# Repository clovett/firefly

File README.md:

# firefly

See [wiki](https://github.com/clovett/firefly/wiki)

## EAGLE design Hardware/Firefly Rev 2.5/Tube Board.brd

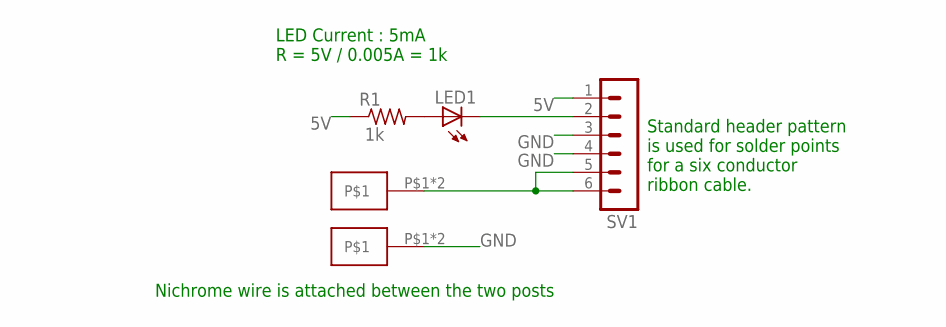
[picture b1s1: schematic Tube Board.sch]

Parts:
LED1: LED_ESML0603; LED_SML0603
R1: R-US_R0603; R0603
SV1: MA06-1
U$1, U$2: A29938CT

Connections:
5V: R1.1, SV1.1
GND: SV1.3, SV1.4, U$2.P$1, U$2.P$2
unnamed: SV1.5, SV1.6, U$1.P$1, U$1.P$2
unnamed: LED1.A, R1.2
unnamed: LED1.C, SV1.2

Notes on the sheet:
Nichrome wire is attached between the two posts
LED Current : 5mA R = 5V / 0.005A = 1k
Standard header pattern is used for solder points for a six conductor ribbon cable.

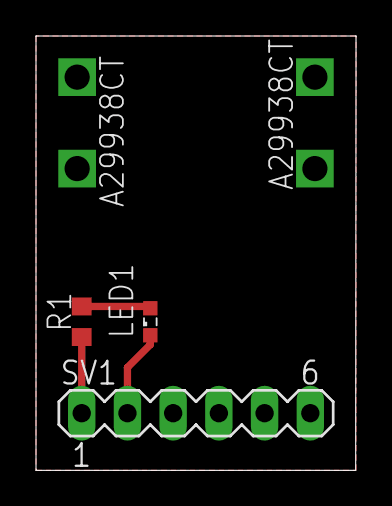
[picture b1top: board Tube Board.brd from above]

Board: 2 copper layers, 17.8 x 24.1 mm, 5 parts (0 on the bottom side), 5 nets.

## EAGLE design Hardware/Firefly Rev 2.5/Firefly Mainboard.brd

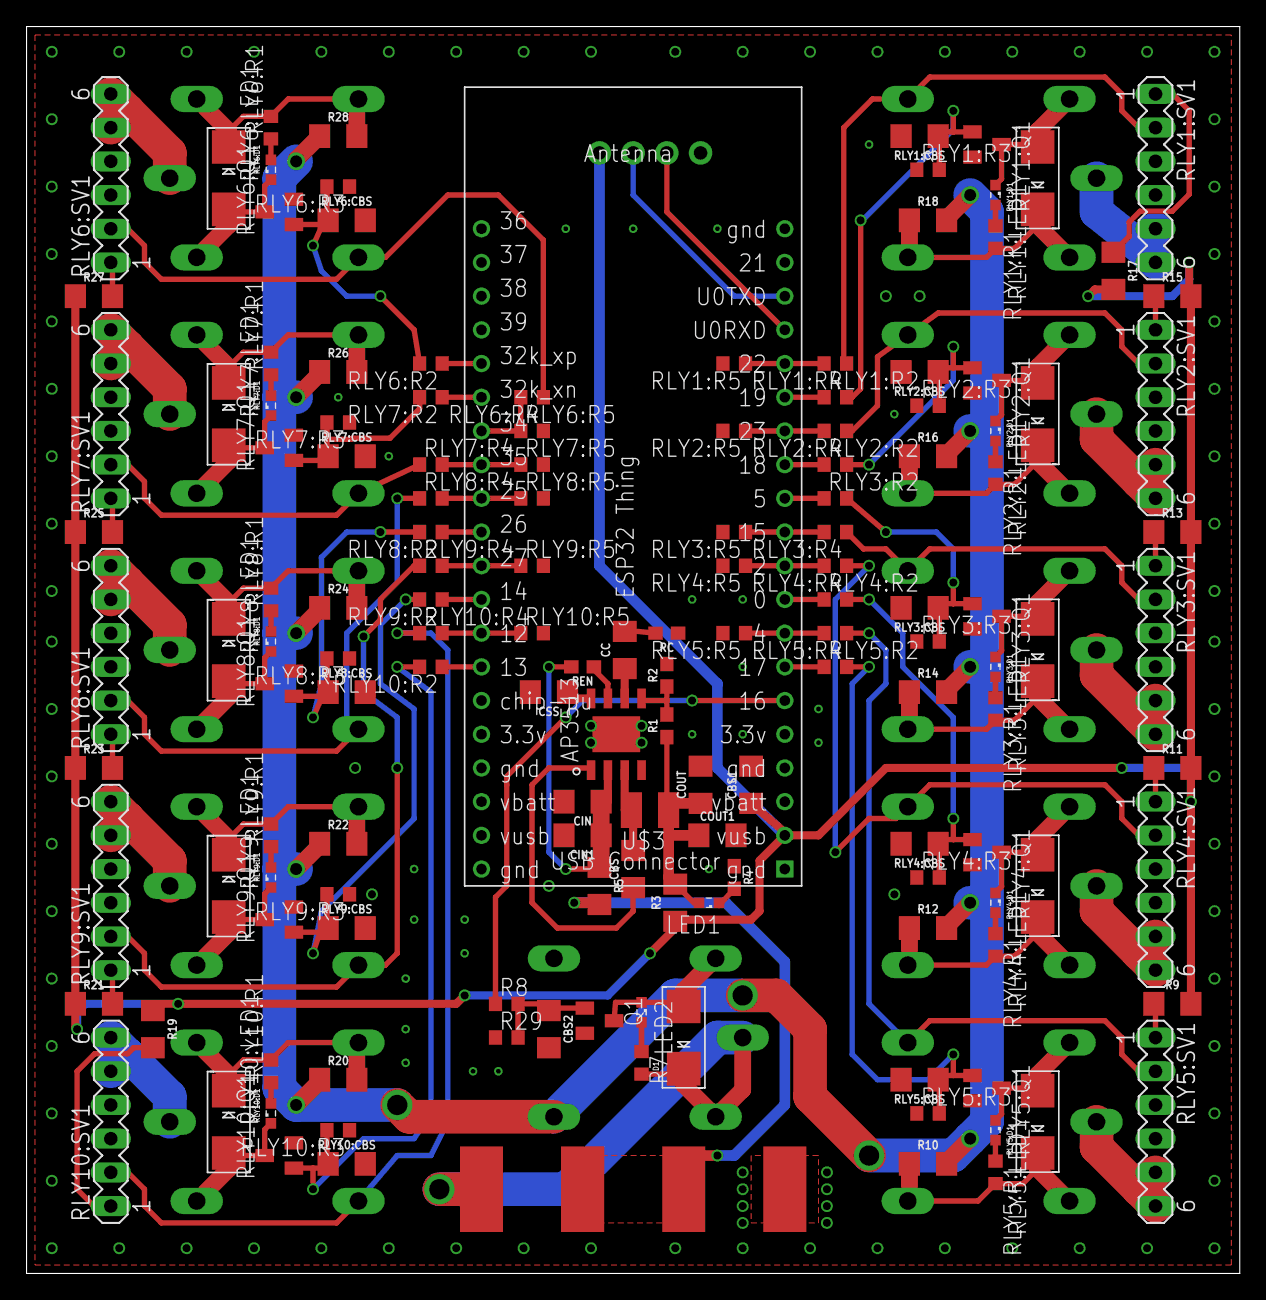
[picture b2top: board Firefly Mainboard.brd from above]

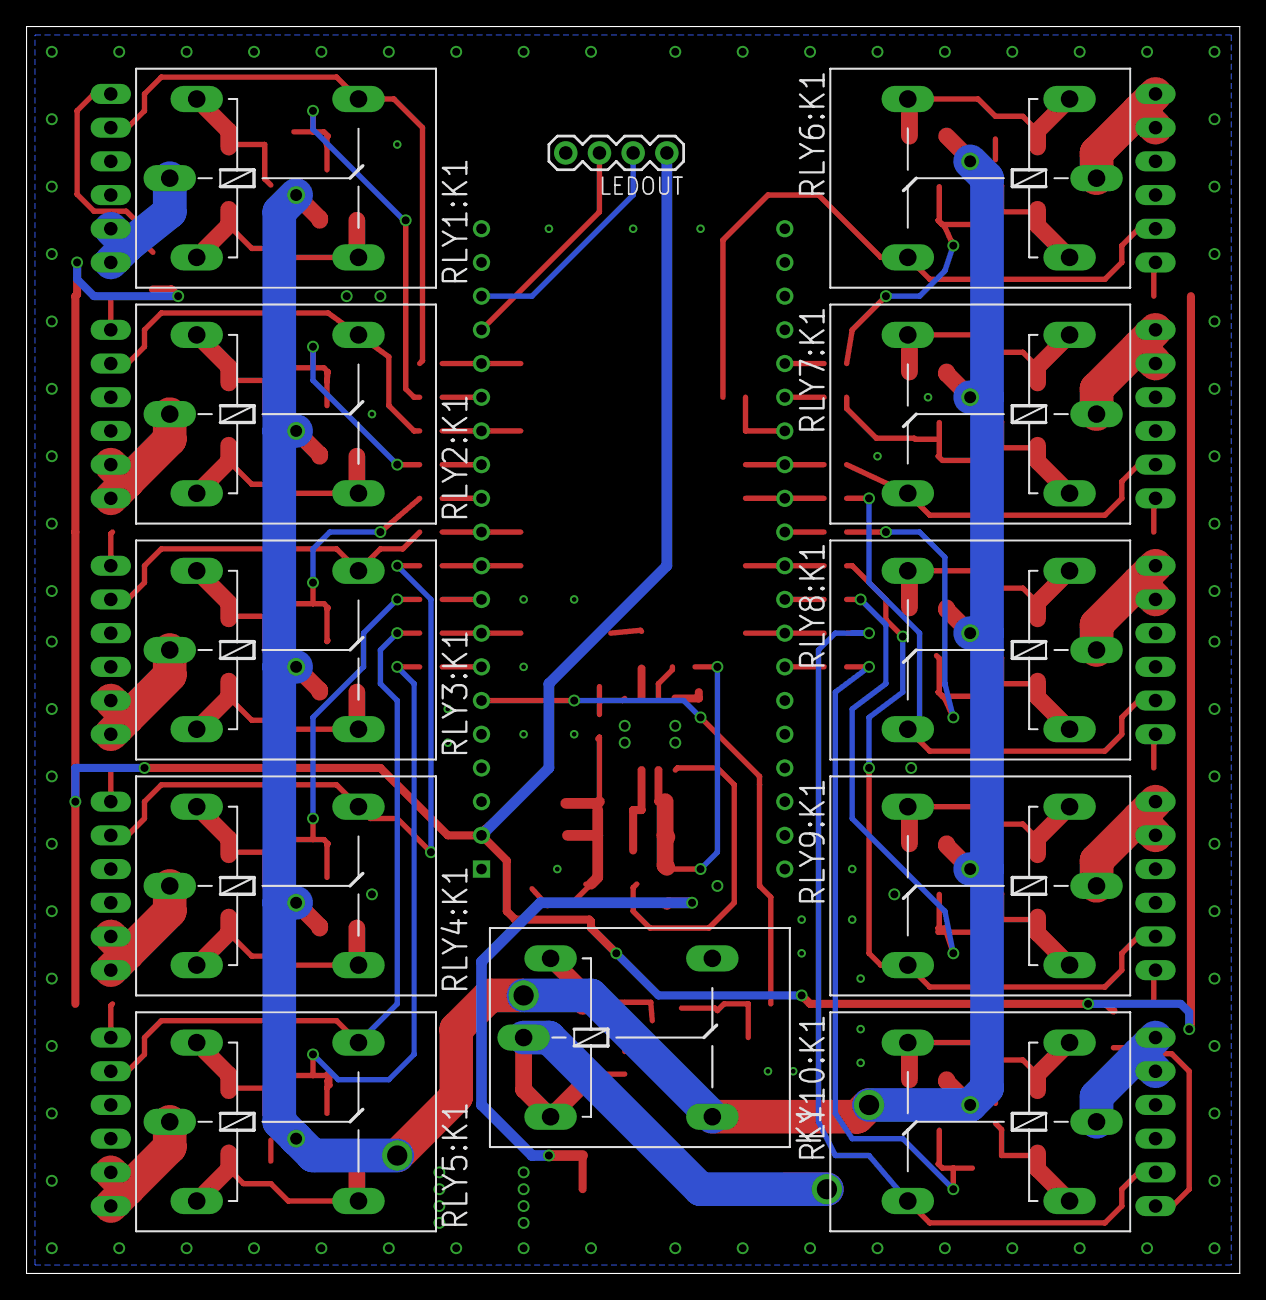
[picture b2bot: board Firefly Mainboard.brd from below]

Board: 2 copper layers, 91.4 x 94.0 mm, 160 parts (12 on the bottom side), 111 nets.

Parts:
CBS: 10nF; 1206
CBS1: 0.1uF; 1206
CBS2: 220nF; 1206
CC: 3.3nF; 1206
CIN, CIN1: 10uF; 1206
COUT, COUT1: 22uF; 1206
CSS: 1.0uF; 1206
D1: SMADIODE
K1: G5LE
LED1, LED2: LED_SML0603
LEDOUT: 1X4-BIG; 1X04-BIG
Q1: BCF32SMD; SOT23-BEC
R1: 10k\; 0603
R2: 2.26k; 0603
R3, R5, R9, R10, R11, R12, R13, R14, R15, R16, R17, R18, R19, R20, R21, R22, R23, R24, R25, R26, R27, R28: 0; 1206
R4: 1k; 0603
R7, R8: R0603
R29: 10k; R0603
RC: 13k; 0603
REN: 100k; 0603
RLY1:CBS, RLY2:CBS, RLY3:CBS, RLY4:CBS, RLY5:CBS, RLY6:CBS, RLY7:CBS, RLY8:CBS, RLY9:CBS, RLY10:CBS: 220nF; 1206
RLY1:D1, RLY2:D1, RLY3:D1, RLY4:D1, RLY5:D1, RLY6:D1, RLY7:D1, RLY8:D1, RLY9:D1, RLY10:D1: SMADIODE
RLY1:K1, RLY2:K1, RLY3:K1, RLY4:K1, RLY5:K1, RLY6:K1, RLY7:K1, RLY8:K1, RLY9:K1, RLY10:K1: G5LE
RLY1:LED1, RLY2:LED1, RLY3:LED1, RLY4:LED1, RLY5:LED1, RLY6:LED1, RLY7:LED1, RLY8:LED1, RLY9:LED1, RLY10:LED1: LED_SML0603
RLY1:Q1, RLY2:Q1, RLY3:Q1, RLY4:Q1, RLY5:Q1, RLY6:Q1, RLY7:Q1, RLY8:Q1, RLY9:Q1, RLY10:Q1: BCF32SMD; SOT23-BEC
RLY1:R1, RLY1:R2, RLY2:R1, RLY2:R2, RLY3:R1, RLY3:R2, RLY4:R1, RLY4:R2, RLY5:R1, RLY5:R2, RLY6:R1, RLY6:R2, RLY7:R1, RLY7:R2, RLY8:R1, RLY8:R2, RLY9:R1, RLY9:R2, RLY10:R1, RLY10:R2: R0603
RLY1:R3, RLY1:R4, RLY2:R3, RLY2:R4, RLY3:R3, RLY3:R4, RLY4:R3, RLY4:R4, RLY5:R3, RLY5:R4, RLY6:R3, RLY6:R4, RLY7:R3, RLY7:R4, RLY8:R3, RLY8:R4, RLY9:R3, RLY9:R4, RLY10:R3, RLY10:R4: 10k; R0603
RLY1:R5, RLY2:R5, RLY3:R5, RLY4:R5, RLY5:R5, RLY6:R5, RLY7:R5, RLY8:R5, RLY9:R5, RLY10:R5: 15k; R0603
RLY1:SV1, RLY2:SV1, RLY3:SV1, RLY4:SV1, RLY5:SV1, RLY6:SV1, RLY7:SV1, RLY8:SV1, RLY9:SV1, RLY10:SV1: MA06-1
U$1: ESP32_THING
U$2: AP3513E
U$3: L 4.7uH; R1210
U$4, U$5: BATTERY_PADS

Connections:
+5V: CBS1.1, LEDOUT.1, R3.1, R9.2, R11.2, R13.2, R15.2, R17.2, R19.1, R21.1, R23.1, R25.1, R27.1, U$1.P$2
+12V: K1.S, R10.2, R12.2, R14.2, R16.2, R18.2, R20.1, R22.1, R24.1, R26.1, R28.1
EN_RELAY: R8.1, U$1.P$6
GND: CBS1.2, CBS2.2, CIN.2, CIN1.2, COUT.2, COUT1.2, CSS.2, LEDOUT.4, Q1.E, R2.2, R4.1, R29.1, RC.1, RLY1:CBS.2, RLY1:Q1.E, RLY1:R3.1, RLY1:R5.2, RLY1:SV1.3, RLY1:SV1.4, RLY2:CBS.2, RLY2:Q1.E, RLY2:R3.1, RLY2:R5.2, RLY2:SV1.3, RLY2:SV1.4, RLY3:CBS.2, RLY3:Q1.E, RLY3:R3.1, RLY3:R5.2, RLY3:SV1.3, RLY3:SV1.4, RLY4:CBS.2, RLY4:Q1.E, RLY4:R3.1, RLY4:R5.2, RLY4:SV1.3, RLY4:SV1.4, RLY5:CBS.2, RLY5:Q1.E, RLY5:R3.1, RLY5:R5.2, RLY5:SV1.3, RLY5:SV1.4, RLY6:CBS.2, RLY6:Q1.E, RLY6:R3.1, RLY6:R5.2, RLY6:SV1.3, RLY6:SV1.4, RLY7:CBS.2, RLY7:Q1.E, RLY7:R3.1, RLY7:R5.2, RLY7:SV1.3, RLY7:SV1.4, RLY8:CBS.2, RLY8:Q1.E, RLY8:R3.1, RLY8:R5.2, RLY8:SV1.3, RLY8:SV1.4, RLY9:CBS.2, RLY9:Q1.E, RLY9:R3.1, RLY9:R5.2, RLY9:SV1.3, RLY9:SV1.4, RLY10:CBS.2, RLY10:Q1.E, RLY10:R3.1, RLY10:R5.2, RLY10:SV1.3, RLY10:SV1.4, U$1.P$1, U$1.P$20, U$1.P$21, U$1.P$24, U$2.EP, U$2.GND, U$4.P2
unnamed: R1.2, R2.1, U$2.FB
unnamed: CC.1, U$2.COMP
unnamed: CC.2, RC.2
unnamed: CSS.1, U$2.SS
unnamed: REN.1, U$2.EN
unnamed: LEDOUT.2, U$1.P$18
unnamed: CBS.2, U$2.SW, U$3.2
unnamed: CBS.1, U$2.BS
unnamed: RLY5:R2.1, U$1.P$7
unnamed: RLY5:R4.2, RLY5:R5.1, U$1.P$8
unnamed: RLY4:R2.1, U$1.P$9
unnamed: RLY4:R4.2, RLY4:R5.1, U$1.P$10
unnamed: RLY3:R2.1, U$1.P$12
unnamed: RLY3:R4.2, RLY3:R5.1, U$1.P$11
unnamed: RLY2:R2.1, U$1.P$13
unnamed: RLY2:R4.2, RLY2:R5.1, U$1.P$14
unnamed: RLY10:R2.1, U$1.P$27
unnamed: RLY10:R4.2, RLY10:R5.1, U$1.P$28
unnamed: RLY9:R2.1, U$1.P$29
unnamed: RLY9:R4.2, RLY9:R5.1, U$1.P$30
unnamed: RLY8:R2.1, U$1.P$31
unnamed: RLY8:R4.2, RLY8:R5.1, U$1.P$32
unnamed: RLY7:R2.1, U$1.P$35
unnamed: RLY7:R4.2, RLY7:R5.1, U$1.P$33
unnamed: RLY6:R2.1, U$1.P$36
unnamed: RLY6:R4.2, RLY6:R5.1, U$1.P$34
unnamed: COUT.1, COUT1.1, LED1.A, R1.1, R3.2, U$3.1
unnamed: LED1.C, R4.2
unnamed: D1.A, K1.2, LED2.C, Q1.C
unnamed: RLY1:R2.1, U$1.P$15
unnamed: CIN.1, CIN1.1, R5.1, REN.2, U$2.IN
unnamed: LED2.A, R7.1
unnamed: R10.1, RLY5:D1.C, RLY5:K1.1, RLY5:K1.S, RLY5:R1.2
unnamed: R9.1, RLY5:SV1.1
unnamed: R11.1, RLY4:SV1.1
unnamed: R12.1, RLY4:D1.C, RLY4:K1.1, RLY4:K1.S, RLY4:R1.2
unnamed: R13.1, RLY3:SV1.1
unnamed: R14.1, RLY3:D1.C, RLY3:K1.1, RLY3:K1.S, RLY3:R1.2
unnamed: R15.1, RLY2:SV1.1
unnamed: R16.1, RLY2:D1.C, RLY2:K1.1, RLY2:K1.S, RLY2:R1.2
unnamed: R17.1, RLY1:SV1.1
unnamed: R18.1, RLY1:D1.C, RLY1:K1.1, RLY1:K1.S, RLY1:R1.2
unnamed: R19.2, RLY10:SV1.1
unnamed: R20.2, RLY10:D1.C, RLY10:K1.1, RLY10:K1.S, RLY10:R1.2
unnamed: R21.2, RLY9:SV1.1
unnamed: R22.2, RLY9:D1.C, RLY9:K1.1, RLY9:K1.S, RLY9:R1.2
unnamed: R23.2, RLY8:SV1.1
unnamed: R24.2, RLY8:D1.C, RLY8:K1.1, RLY8:K1.S, RLY8:R1.2
unnamed: R25.2, RLY7:SV1.1
unnamed: R26.2, RLY7:D1.C, RLY7:K1.1, RLY7:K1.S, RLY7:R1.2
unnamed: R27.2, RLY6:SV1.1
unnamed: R28.2, RLY6:D1.C, RLY6:K1.1, RLY6:K1.S, RLY6:R1.2
unnamed: RLY1:R4.2, RLY1:R5.1, U$1.P$16
unnamed: D1.C, K1.1, K1.P, R7.2, U$5.P1
unnamed: CBS2.1, Q1.B, R8.2, R29.2
RLY1:N$1: RLY1:LED1.A, RLY1:R1.1
RLY1:N$2: RLY1:K1.P, RLY1:SV1.5, RLY1:SV1.6
RLY1:N$3: RLY1:CBS.1, RLY1:Q1.B, RLY1:R2.2, RLY1:R3.2
RLY1:N$4: RLY1:D1.A, RLY1:K1.2, RLY1:LED1.C, RLY1:Q1.C
RLY1:N$6: RLY1:K1.O, RLY1:R4.1, RLY1:SV1.2
RLY2:N$1: RLY2:LED1.A, RLY2:R1.1
RLY2:N$2: RLY2:K1.P, RLY2:SV1.5, RLY2:SV1.6
RLY2:N$3: RLY2:CBS.1, RLY2:Q1.B, RLY2:R2.2, RLY2:R3.2
RLY2:N$4: RLY2:D1.A, RLY2:K1.2, RLY2:LED1.C, RLY2:Q1.C
RLY2:N$6: RLY2:K1.O, RLY2:R4.1, RLY2:SV1.2
RLY3:N$1: RLY3:LED1.A, RLY3:R1.1
RLY3:N$2: RLY3:K1.P, RLY3:SV1.5, RLY3:SV1.6
RLY3:N$3: RLY3:CBS.1, RLY3:Q1.B, RLY3:R2.2, RLY3:R3.2
RLY3:N$4: RLY3:D1.A, RLY3:K1.2, RLY3:LED1.C, RLY3:Q1.C
RLY3:N$6: RLY3:K1.O, RLY3:R4.1, RLY3:SV1.2
RLY4:N$1: RLY4:LED1.A, RLY4:R1.1
RLY4:N$2: RLY4:K1.P, RLY4:SV1.5, RLY4:SV1.6
RLY4:N$3: RLY4:CBS.1, RLY4:Q1.B, RLY4:R2.2, RLY4:R3.2
RLY4:N$4: RLY4:D1.A, RLY4:K1.2, RLY4:LED1.C, RLY4:Q1.C
RLY4:N$6: RLY4:K1.O, RLY4:R4.1, RLY4:SV1.2
RLY5:N$1: RLY5:LED1.A, RLY5:R1.1
RLY5:N$2: RLY5:K1.P, RLY5:SV1.5, RLY5:SV1.6
RLY5:N$3: RLY5:CBS.1, RLY5:Q1.B, RLY5:R2.2, RLY5:R3.2
RLY5:N$4: RLY5:D1.A, RLY5:K1.2, RLY5:LED1.C, RLY5:Q1.C
RLY5:N$6: RLY5:K1.O, RLY5:R4.1, RLY5:SV1.2
RLY6:N$1: RLY6:LED1.A, RLY6:R1.1
RLY6:N$2: RLY6:K1.P, RLY6:SV1.5, RLY6:SV1.6
RLY6:N$3: RLY6:CBS.1, RLY6:Q1.B, RLY6:R2.2, RLY6:R3.2
RLY6:N$4: RLY6:D1.A, RLY6:K1.2, RLY6:LED1.C, RLY6:Q1.C
RLY6:N$6: RLY6:K1.O, RLY6:R4.1, RLY6:SV1.2
RLY7:N$1: RLY7:LED1.A, RLY7:R1.1
RLY7:N$2: RLY7:K1.P, RLY7:SV1.5, RLY7:SV1.6
RLY7:N$3: RLY7:CBS.1, RLY7:Q1.B, RLY7:R2.2, RLY7:R3.2
RLY7:N$4: RLY7:D1.A, RLY7:K1.2, RLY7:LED1.C, RLY7:Q1.C
RLY7:N$6: RLY7:K1.O, RLY7:R4.1, RLY7:SV1.2
RLY8:N$1: RLY8:LED1.A, RLY8:R1.1
RLY8:N$2: RLY8:K1.P, RLY8:SV1.5, RLY8:SV1.6
RLY8:N$3: RLY8:CBS.1, RLY8:Q1.B, RLY8:R2.2, RLY8:R3.2
RLY8:N$4: RLY8:D1.A, RLY8:K1.2, RLY8:LED1.C, RLY8:Q1.C
RLY8:N$6: RLY8:K1.O, RLY8:R4.1, RLY8:SV1.2
RLY9:N$1: RLY9:LED1.A, RLY9:R1.1
RLY9:N$2: RLY9:K1.P, RLY9:SV1.5, RLY9:SV1.6
RLY9:N$3: RLY9:CBS.1, RLY9:Q1.B, RLY9:R2.2, RLY9:R3.2
RLY9:N$4: RLY9:D1.A, RLY9:K1.2, RLY9:LED1.C, RLY9:Q1.C
RLY9:N$6: RLY9:K1.O, RLY9:R4.1, RLY9:SV1.2
RLY10:N$1: RLY10:LED1.A, RLY10:R1.1
RLY10:N$2: RLY10:K1.P, RLY10:SV1.5, RLY10:SV1.6
RLY10:N$3: RLY10:CBS.1, RLY10:Q1.B, RLY10:R2.2, RLY10:R3.2
RLY10:N$4: RLY10:D1.A, RLY10:K1.2, RLY10:LED1.C, RLY10:Q1.C
RLY10:N$6: RLY10:K1.O, RLY10:R4.1, RLY10:SV1.2
SCL: LEDOUT.3, U$1.P$17
VBATT: R5.2, U$4.P1, U$5.P2

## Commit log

2016-07-03 added arduino code from last year, starting to rework it now.
2016-07-04 messaging is working, the fire control logic is in progress
2016-07-04 firing logic is done, but untested.
2016-07-04 adjusted the messaging system.
2016-07-04 windows app to control fireworks.
2016-07-04 fixed tube port problem
2016-07-04 Fix bugs
2016-07-04 Fix bugs.
2016-07-04 commiting zachs changes before merging in chris's work
2016-07-04 Fix Touch UI states.
2016-07-04 final code for the 2016 show.
2016-07-04 Add patterns.
2016-07-04 Add icon
2016-07-05 Add more patterns.
2016-07-05 add some error handling.
2016-07-05 relaxed the heartbeat logic on the arduino
2016-07-05 Bug fixes.
2016-07-05 Update artwork
2016-07-05 Code cleanup
2016-09-20 outlining basics of networking module
2016-09-20 basic networking udp rxtx working.
2016-09-20 started revamping the connection methods and structure
2016-09-20 removing network class in favor of connection, client, and server classes.
2016-09-20 new networking system basics are working.
2016-09-21 networking connection and reconection is working.
2016-09-21 networking module mostly d finished
2016-09-21 fixed networking bug c unhandeled exception when sending data.
2016-09-21 adjusted blocking times fofor networking
2016-10-25 changed networking code to allow for reuse of the udp broadcast port, and to better handle shutdowns of the server and client.
2016-10-25 starting to implement state and network protocol on the simnode.
2016-10-26 started making changed to sim node to fill out final system logic, and added timeouts to the client udp listen socket in the networking file.
2016-10-26 outlining sim node logic is done other than the message handler
2016-10-26 going to bed, but I made a tubes class and got the loading logic sorted.
2016-10-27 work in progress commit.
2016-10-27 started working on a messages.py module to provide easier message handling.
2016-10-27 seperated crc and simular functions to a utils.py file
2016-10-28 packing and unpacking for messages is done, now to write the action handler for the slave.
2016-10-28 basic message parsing is working on the slave side. Need to add logic to the actions, and then start work on the basic master.
2016-10-28 starting to fill out action logic.
2016-10-29 basics of the simulation module are done, working on functions for the master so that a total system test may be run.
2016-10-29 started basic master logic.
2016-10-31 basic master-slave coms seem to be working. Now working to clean up master side interactions
2016-11-01 new server code is updated with functions for reports, firing, and heartbeats.
2016-11-07 changed the bind operation in networking to use ''instead of hostname
2016-11-09 WIP commit for refactor of message and networking to better abstract message handling and parsing.
2016-11-10 majority of refactor is finished, now need to clean up the code for closing connections and decide on what should happen when messages fall out of sync.
2016-11-10 still need to figure out what to do when messages get out of sync, but most of the changes are done.
2016-11-11 Add vs projects
2016-11-11 started to build the error passing system for tcpstream.
2016-11-12 first pass at error handleing done. There are still some annoying performance issues that I would like to get to in dealing with larger number of tubes, but this should work for our scales.
2016-11-13 found issue in networking.py:Server that was causing failures on windows. Now need to test between mac and window.
2016-11-14 added a printout to networking:server:broadcast_loop for showing the length of the outgoing connection message.
2016-11-14 changed report fetching and updating to make it more robust.
2016-11-14 added use of netifaces module to networking in order to get address detection on macos to work correctly.
2017-05-16 added gpio test
2017-06-14 added eagle files for current board hardware.
2017-06-14 removed the esp_projects folder since it was doing odd things.
2017-06-14 added gpio example for testing relays and leds.
2017-06-19 add beginnings of a c++ framework for hub firmware.
2017-06-20 Fix hostname and cleanup temp files.
2017-06-21 Beginnings of universal app with simple hub discovery using UDP broadcast.
2017-06-22 Get UDP discovery working.
2017-06-23 fix tcpip_adapter_set_hostname
2017-06-25 code tcp socket, not working yet...
2017-06-25 refactor code cleanup
2017-06-26 added uart bridge tcp server example.
2017-06-27 fix tcp connection. implement simple protocol.
2017-06-27 hook up more code
2017-06-28 switching to UDP comm stack only...
2017-06-29 Get it all working !!
2017-06-29 Get things working yay !!!
2017-06-30 Add Arm/disarm button to the windows app. Turn on led strip when hub is armed.
2017-07-01 Add connection state monitoring and auto-reconnect.
2017-07-01 update to correct LED datasheet and fix bugs.
2017-07-01 switch to a more flexible string based protocol. This will allow transmission of variable length error messages over the TCP stream which will be useful for debugging when we have no USB connected.
2017-07-01 Test color setting and fix other bugs.
2017-07-02 Add lights off as an option.
2017-07-02 UI cleanup
2017-07-02 fix scaling of background image
2017-07-02 Add icons and help
2017-07-02 Fix typo
2017-07-02 Publish.
2017-07-02 Fix fullscreen mode
2017-07-03 Add settings and ability to change arm color.
2017-07-03 Add UI for tube sensing.
2017-07-03 Fix layout of command bar buttons.
2017-07-03 Publish
2017-07-03 Fix bugs, add setting for controlling burn time
2017-07-04 Add ability to launch more than one tube at a time. Add tube size scaling control.
2017-07-04 clear messages on refresh
2017-07-04 Add control over play batch size (number of tubes per hub to fire simultaneously).
2017-07-04 balance the explosions.
2017-07-04 Add custom program control.
2017-07-04 add touch input
2017-07-04 Add execution of drawing program.
2017-07-04 Fix layout bugs.
2017-07-05 Don't clear fired state until we get the ACK
2017-11-30 add some help to remind folks how to flash the device.

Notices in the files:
parts and their libraries:
SparkFun-Capacitors: Licensing: Creative Commons ShareAlike 4.0 International - https://creativecommons.org/licenses/by-sa/4.0
